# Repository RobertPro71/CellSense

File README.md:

# CellSense
Measure voltage from a RC cell pack with up to 6 cells. 

To measure the voltage from a RC-Lipo-pack with high reselution. First two cells are convert with a voltage divider. To get the voltage from the second cell it is needed to subtract the voltage from the frist cell. All other cells are converted with a differential amplifier that have "over the top" inputs.

Convert cells from 0..4,5V (pack voltage 27V) to 0..2,5V.

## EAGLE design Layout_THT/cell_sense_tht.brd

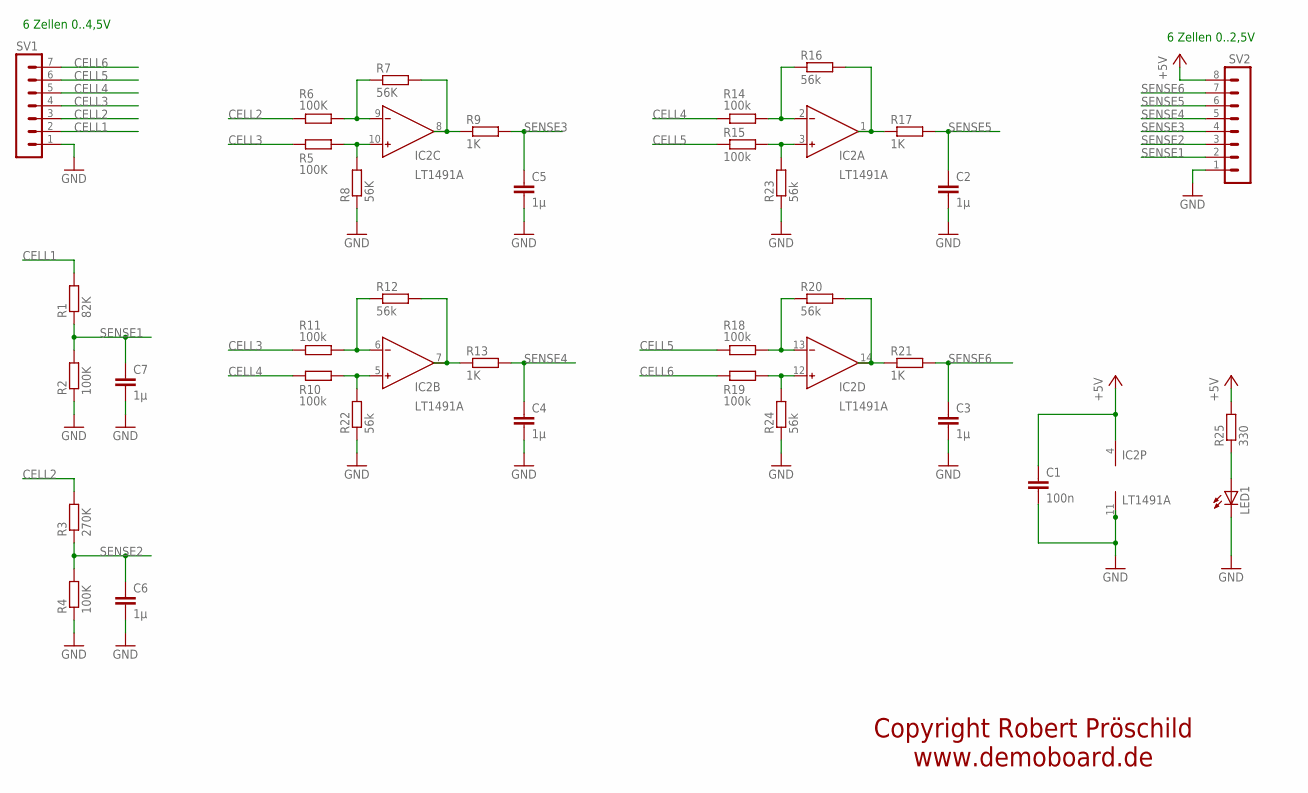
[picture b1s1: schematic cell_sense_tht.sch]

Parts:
C1: 100n; C025-024X044
C2, C3, C4, C5, C6, C7: 1µ; C025-024X044
IC2: LT1491A; DIL14
LED1: LED3MM
R1: 82K; 0204/7
R2, R4, R5, R6: 100K; 0204/7
R3: 270K; 0204/7
R7, R8: 56K; 0204/7
R9, R13, R17, R21: 1K; 0204/7
R10, R11, R14, R15, R18, R19: 100k; 0204/7
R12, R16, R20, R22, R23, R24: 56k; 0204/7
R25: 330; 0204/7
SV1: MA07-1
SV2: MA08-1

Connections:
+5V: C1.1, IC2.4 (V+), R25.2, SV2.8
CELL1: R1.2, SV1.2
CELL2: R3.2, R6.1, SV1.3
CELL3: R5.1, R11.1, SV1.4
CELL4: R10.1, R14.1, SV1.5
CELL5: R15.1, R18.1, SV1.6
CELL6: R19.1, SV1.7
GND: C1.2, C2.2, C3.2, C4.2, C5.2, C6.2, C7.2, IC2.11 (V-), LED1.K (C), R2.1, R4.1, R8.1, R22.1, R23.1, R24.1, SV1.1, SV2.1
unnamed: IC2.10 (IN+), R5.2, R8.2
unnamed: IC2.9 (IN-), R6.2, R7.1
unnamed: IC2.8 (OUT), R7.2, R9.1
unnamed: LED1.A, R25.1
unnamed: IC2.3 (IN+), R15.2, R23.2
unnamed: IC2.2 (IN-), R14.2, R16.1
unnamed: IC2.1 (OUT), R16.2, R17.1
unnamed: IC2.5 (IN+), R10.2, R22.2
unnamed: IC2.6 (IN-), R11.2, R12.1
unnamed: IC2.7 (OUT), R12.2, R13.1
unnamed: IC2.12 (IN+), R19.2, R24.2
unnamed: IC2.13 (IN-), R18.2, R20.1
unnamed: IC2.14 (OUT), R20.2, R21.1
SENSE1: C7.1, R1.1, R2.2, SV2.2
SENSE2: C6.1, R3.1, R4.2, SV2.3
SENSE3: C5.1, R9.2, SV2.4
SENSE4: C4.1, R13.2, SV2.5
SENSE5: C2.1, R17.2, SV2.6
SENSE6: C3.1, R21.2, SV2.7

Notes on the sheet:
6 Zellen 0..4,5V
6 Zellen 0..2,5V
Copyright Robert Pröschild www.demoboard.de

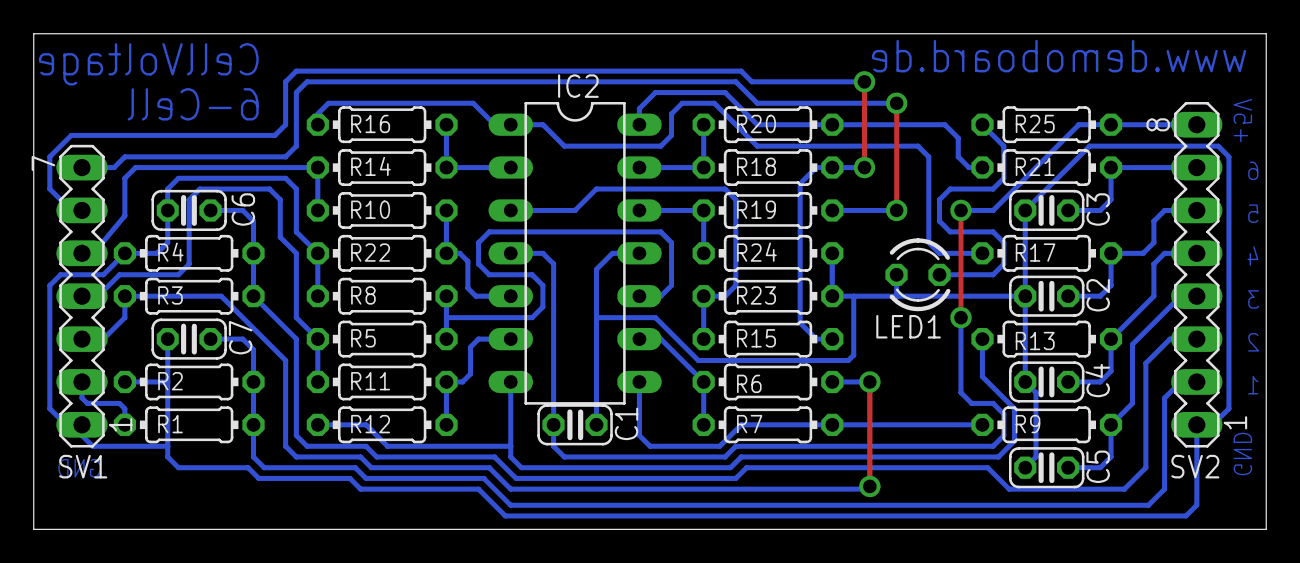
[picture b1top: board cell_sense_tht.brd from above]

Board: 2 copper layers, 73.0 x 29.4 mm, 36 parts (0 on the bottom side), 27 nets.

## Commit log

2017-01-02 First Version
